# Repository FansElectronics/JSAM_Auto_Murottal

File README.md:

# Jadwal Sholat Auto Murottal (JSAM) dengan ESP8266 & ESP32

Firmware pemutar audio otomatis **Jadwal Sholat Auto Murottal (JSAM)** berbasis mikrokontroler ESP8266 dan ESP32 dengan modul audio DFPlayer Mini. Project ini dirancang untuk memutar lantunan Al-Qur'an (Murottal), Tarhim, serta adzan otomatis menjelang dan saat masuk waktu sholat. Perangkat ini dapat beroperasi secara mandiri (**Stand-alone / Auto Mode**) maupun terhubung sebagai penerima wireless (**Slave Mode via ESP-NOW**) yang disinkronkan langsung dengan display [Jadwal Sholat Dot Matrix (JSDM)](https://github.com/FansElectronics/JSDM_WiFi).

Pengaturan jadwal, pemilihan surat/qori, volume, jeda relay amplifier, serta pengujian audio dapat dikonfigurasi langsung melalui aplikasi Android:
👉 **https://play.google.com/store/apps/details?id=com.fanselectronics.jsam**

---

## Spesifikasi Firmware ⚙️:
- **Mikrokontroler**: ESP8266 (Wemos D1 Mini) & ESP32 (DevKitC / NodeMCU)
- **Modul Audio**: DFPlayer Mini MP3 Player (MicroSD FAT32)
- **Penyimpanan Konfigurasi**: LittleFS Flash File System
- **Real-Time Clock (RTC)**: DS3231 I2C RTC (Akurat dengan kompensasi suhu)
- **Komunikasi Display / Pengaturan**: LCD 16x2 / 20x4 I2C (untuk status & navigasi)
- **Kontrol Daya Audio**: 1 Relay Paralel (Master Power Amplifier Audio Luar & Dalam)
- **Mode Operasi Fleksibel**:
  - **Mode AUTO (Stand-alone)**: Menghitung jadwal sholat mandiri via RTC internal dan menjalankan urutan playlist otomatis.
  - **Mode SLAVE (Wireless Receiver)**: Menerima pemicu jadwal, trigger audio, dan status sholat dari master JSDM secara nirkabel via **ESP-NOW**.
- **Konektivitas Konfigurasi**: Wi-Fi Access Point (Web/WebSocket/JSON API) terintegrasi ke Aplikasi Android.
- **Proteksi Flash**: Fitur reset pabrik / wipe LittleFS cepat dengan menahan tombol saat booting.

---

## Fitur yang Tersedia ✅:
- **Penjadwalan Playlist Per Sholat**: Konfigurasi mandiri untuk 5 waktu sholat (Subuh, Dzuhur, Ashar, Maghrib, Isya').
- **Pemisahan Audio Adzan Otomatis**:
  - Pemilihan tipe alarm: Buzzer Beep atau Suara MP3 Adzan penuh.
  - Pemisahan folder otomatis internal (Folder `02` untuk Adzan Subuh, Folder `01` untuk Adzan Reguler).
- **Katalog Qori & Audio Khusus**:
  - Mendukung pembacaan surat dinamis per Qori (Juz 30 maupun 114 Surat lengkap).
  - Folder khusus untuk Sholawat Tarhim dan audio kustom lainnya.
- **Sinkronisasi Database Cloud**: Database metadata surat, qori, dan durasi audio terhubung online via GitHub RAW dan tersimpan otomatis di perangkat.
- **Pencegahan Letupan Suara Amplifier**: Dilengkapi pengaturan jeda nyala relay sebelum audio berbunyi (*Delay Play*) dan jeda mati relay setelah audio tuntas (*Delay Stop/Adzan*).
- **Tombol Multifungsi Cerdas**:
  - *Klik Cepat saat Audio Berbunyi*: Menghentikan audio Murottal/Adzan seketika jika ingin adzan atau tilawah manual tanpa merusak timer jadwal.
  - *Tahan 10 Detik di Loop*: Beralih mode operasi secara instan (Mode AUTO ⟷ Mode SLAVE).
  - *Tahan 10 Detik Saat Boot*: Format total partisi LittleFS (Factory Reset / Wipe All Data).
- **Upload Lisensi & Firmware Update**: Mendukung upload `license.json` dan flashing via WebSerial Flasher.

---

## Struktur Folder MicroSD (DFPlayer Mini) 📁:
Untuk memastikan sistem pemutar audio membaca file dengan tepat, susun berkas MP3 di dalam MicroSD dengan format folder 2 digit angka:
```text
MicroSD Root/
├── 01/             -> Adzan Reguler (Dzuhur, Ashar, Maghrib, Isya) [001.mp3, 002.mp3, ...]
├── 02/             -> Adzan Subuh [001.mp3, 002.mp3, ...]
├── 03/             -> Audio Khusus / Tarhim [001.mp3, 002.mp3, ...]
├── 04 - 10/        -> Cadangan Audio Masa Depan
└── 11+/            -> Folder Qori Al-Qur'an (11 = Qori 1, 12 = Qori 2, dst.)
```
*Catatan: Pastikan MicroSD diformat FAT32 dan file audio MP3 diunduh di [RILIS TAG MP3 FILE](https://github.com/FansElectronics/JSAM_Auto_Murottal/releases/tag/MP3).* Kami menerima sumbangan file mp3 jika ingin berkontribusi.

---

## Default Access Point (Mode Pengaturan) 📶:
```text
    SSID: JSAM Auto Murottal
    PASS: fanselectronics
```

---

## Bagaimana Sistem Lisensinya? 🔐

Sistem lisensi firmware JSAM Auto Murottal menggunakan enkripsi berbasis **ID Perangkat Keras Unik (Device ID)** pada setiap chip ESP8266 / ESP32. 

- **Mode SLAVE (Gratis / Tanpa Lisensi)**: Jika Anda menggunakan modul ini murni sebagai penerima nirkabel dari JSDM WiFi / RGB, modul dapat bekerja langsung tanpa aktivasi berbayar, dengan syarat lisensi JSDM Murottal aktif.
- **Mode AUTO (Berlisensi Stand-Alone)**: Membutuhkan lisensi aktif untuk mengaktifkan perhitungan jadwal mandiri, RTC DS3231, dan playlist otomatis tanpa bergantung pada master JSDM.

Untuk melakukan aktivasi:
1. Hubungkan aplikasi Android ke sinyal Wi-Fi modul JSAM.
2. Buka menu **Aktivasi / Lisensi**, lalu salin **Device ID** yang tampil.
3. Hubungi kontak resmi Fans Electronics untuk mendapatkan file `license.json`.
4. Unggah berkas `license.json` langsung melalui aplikasi Android atau tool web flasher.

Dana pembelian lisensi ini digunakan langsung untuk mendukung riset berkelanjutan, pemeliharaan pustaka, serta penambahan fitur-fitur firmware baru.

**Harga Lisensi JSAM Stand-Alone 🏷️:**
- Lisensi JSAM Stand-Alone Mode (ESP8266 / ESP32): **Rp. 150,000**

**Syarat dan Ketentuan Lisensi 📜:** 
- Lisensi berlaku mutlak untuk 1 (satu) chip ESP8266 atau ESP32 karena mengikat berdasarkan ID unik perangkat keras.
- Garansi lisensi berlaku apabila chip rusak secara fisik dan kirim chip rusak kepada kami sebagai bukti. Jika chip tidak dapat dikirim, wajib membeli lisensi baru.
- Garansi berlaku 1 tahun dari license diterbitkan.
- Pembelian pihak kedua/ketiga tetap dilayani sesuai syarat di atas selama ID unik terdaftar resmi di database kami.

---

## Sistem Pembayaran & Donasi 💵

- **Pemesanan Lisensi & Bantuan Teknis**: https://wa.me/6281803750001
- **Dukungan Donasi Riset**: https://saweria.co/fanselectronics

---

## Cara Flash Firmware & Upload Lisensi 🚀
Anda dapat melakukan kompilasi mandiri atau menggunakan tool browser flasher WebSerial resmi dari Fans Electronics tanpa perlu instalasi IDE yang rumit:
- **JSAM Firmware Flasher**: https://app.fanselectronics.com/flasher/JSAM/
- **License Uploader Tool**: https://app.fanselectronics.com/tools/license-uploader
- **File Audio MP3 Murottal**: https://github.com/FansElectronics/JSAM_Auto_Murottal/releases/tag/MP3

---

## Diagram Wiring & Skematik Hardware 💾

|Definisi | Pin ESP32 | Pin ESP8266 | Keterangan |
| :--- | :--- | :--- | :--- |
| **MP3_RX** | GPIO 33 | D5 | Terhubung ke pin TX MP3 Modul |
| **MP3_TX** | GPIO 25 | D6 | Terhubung ke pin RX MP3 Modul & Resistor 1K |
| **MP3_BUSY** | GPIO 26 | D7 | Pin indikator status sibuk modul MP3 |
| **RELAY** | GPIO 27 | D8 | Pin kontrol Relay |
| **BUZZER** | GPIO 15 | D4 | Pin kontrol Buzzer |
| **BUTTON** | GPIO 13 | D3 | Pin input Tombol / Button |
| **LED** | GPIO 2 | D0 | Pin kontrol LED |
| **I2C SDA** | GPIO 21 | D2 | Pin kontrol LED |
| **I2C SCL** | GPIO 22 | D1 | Pin kontrol LED |

File desain skematik dan layout PCB lengkap dapat diunduh pada folder `/PCB` di repository ini.

### Skematik ESP8266 Wemos D1 Mini 2 Relay

---

## Terima Kasih Kepada 🤲
- Allah Subhanahu Wa Ta'ala
- Arduino.cc
- GitHub
- Kontributor MP3 Files, dll
- Semua orang yang mentraktir saya kopi

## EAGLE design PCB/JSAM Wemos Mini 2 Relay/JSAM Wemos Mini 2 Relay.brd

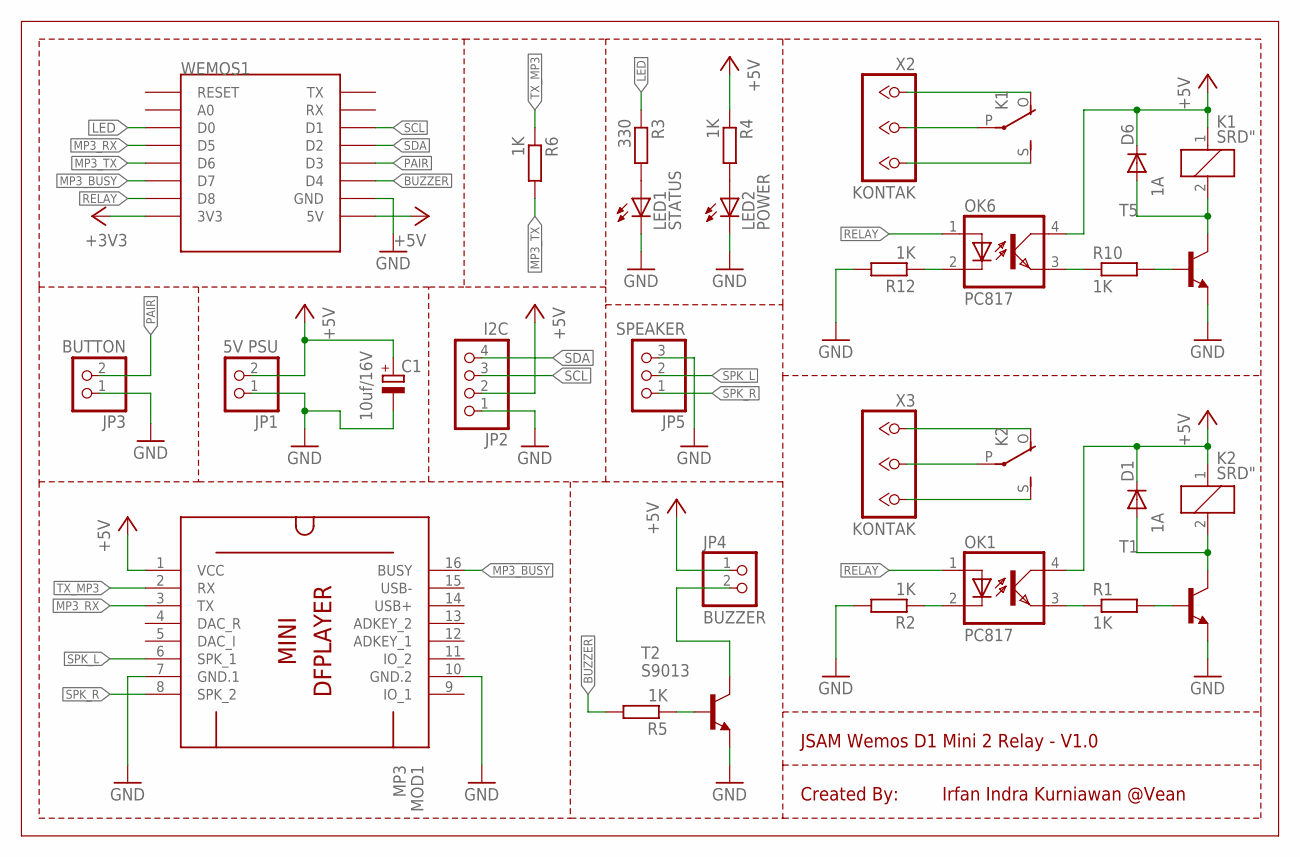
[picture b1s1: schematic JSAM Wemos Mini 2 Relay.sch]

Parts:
C1: 10uf/16V; E2,5-7
D1, D6: 1A; D40-10
JP1: 5V PSU; 1X02
JP2: I2C; 1X04
JP3: BUTTON; 1X02
JP4: BUZZER; 1X02
JP5: SPEAKER; 1X03
K1, K2: SRD"; SRD
LED1: STATUS; LED3MM
LED2: POWER; LED3MM
MOD1: MP3; DFPLAYER-MINI-MODULE
OK1, OK6: PC817; DIL04
R1, R2, R10, R12: 1K; 0207/7
R3: 330; 0207/10
R4: 1K; 0207/10
R5, R6: 1K; 0207/12
T1, T5: BC317-NPN-TO92-EBC; TO92-EBC
T2: S9013; TO92-EBC
WEMOS1: WEMOS-D1-MINI
X2, X3: KONTAK; KL3

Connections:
+3V3: WEMOS1.3V3
+5V: C1.+, D1.C, D6.C, JP1.2, JP2.2, JP4.1, K1.1, K2.1, MOD1.1 (VCC), OK1.4 (COL), OK6.4 (COL), R4.1, WEMOS1.5V
BUZZER: R5.2, WEMOS1.D4
GND: C1.-, JP1.1, JP2.1, JP3.1, JP5.3, LED1.K (C), LED2.K (C), MOD1.7 (GND.1), MOD1.10 (GND.2), R2.2, R12.2, T1.E, T2.E, T5.E, WEMOS1.GND
LED: R3.1, WEMOS1.D0
MP3_BUSY: MOD1.16 (BUSY), WEMOS1.D7
MP3_RX: MOD1.3 (TX), WEMOS1.D5
MP3_TX: R6.2, WEMOS1.D6
unnamed: K1.P (COM), X2.2
unnamed: K1.O (NC), X2.1
unnamed: K1.S (NO), X2.3
unnamed: R1.2, T1.B
unnamed: OK1.3 (EMIT), R1.1
unnamed: OK1.2 (C), R2.1
unnamed: D1.A, K2.2, T1.C
unnamed: K2.O (NC), X3.1
unnamed: K2.P (COM), X3.2
unnamed: K2.S (NO), X3.3
unnamed: LED1.A, R3.2
unnamed: LED2.A, R4.2
unnamed: JP4.2, T2.C
unnamed: R5.1, T2.B
unnamed: R10.2, T5.B
unnamed: OK6.3 (EMIT), R10.1
unnamed: OK6.2 (C), R12.1
unnamed: D6.A, K1.2, T5.C
PAIR: JP3.2, WEMOS1.D3
RELAY: OK1.1 (A), OK6.1 (A), WEMOS1.D8
SCL: JP2.3, WEMOS1.D1
SDA: JP2.4, WEMOS1.D2
SPK_L: JP5.2, MOD1.6 (SPK_1)
SPK_R: JP5.1, MOD1.8 (SPK_2)
TX_MP3: MOD1.2 (RX), R6.1

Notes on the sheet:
JSAM Wemos D1 Mini 2 Relay - V1.0
Created By:
Irfan Indra Kurniawan @Vean

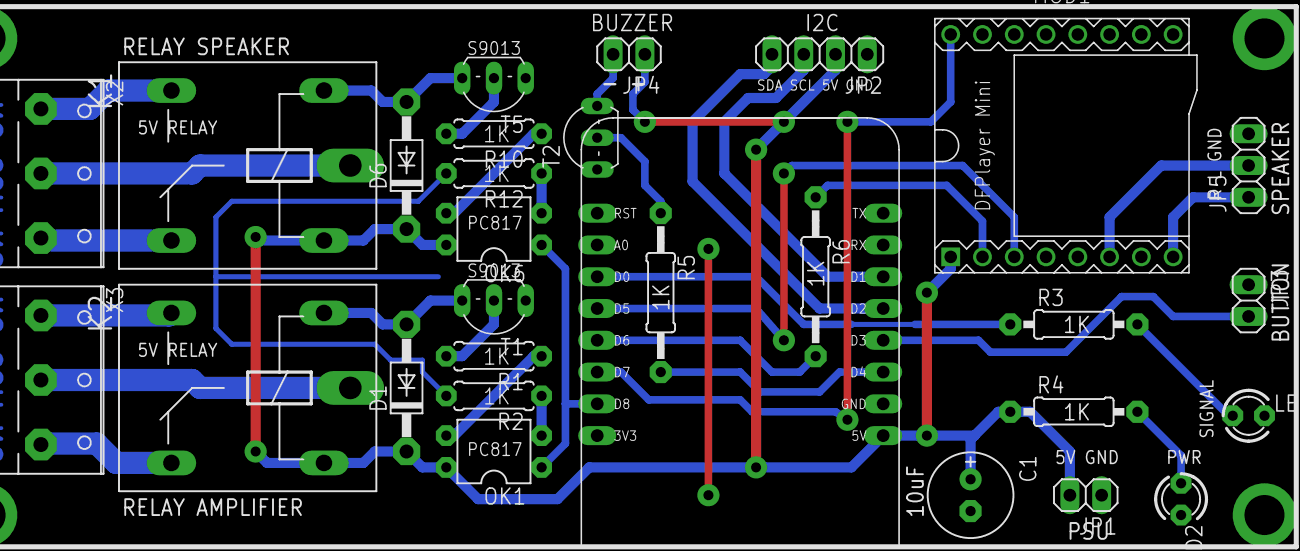
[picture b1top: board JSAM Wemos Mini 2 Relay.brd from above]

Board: 2 copper layers, 29 parts (0 on the bottom side), 32 nets.

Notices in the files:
parts and their libraries:
diy-modules: Released under the Creative Commons Attribution 4.0 International License: http://creativecommons.org/licenses/by/4.0
